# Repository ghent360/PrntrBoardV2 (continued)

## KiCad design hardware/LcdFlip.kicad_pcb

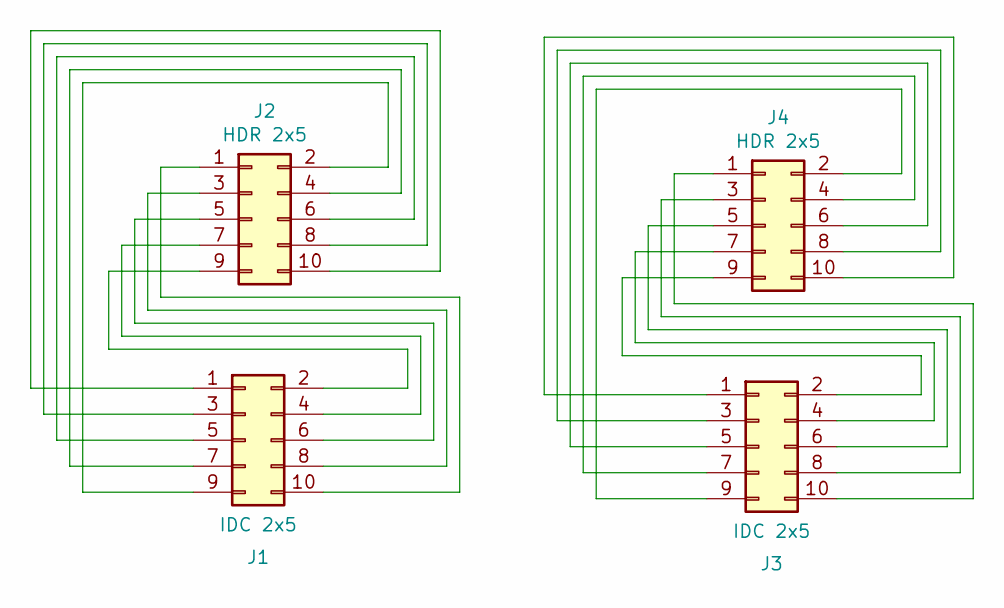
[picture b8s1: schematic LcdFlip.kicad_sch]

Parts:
J1, J3: IDC 2x5
J2, J4: HDR 2x5

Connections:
unnamed: J1.1, J2.10
unnamed: J1.2, J2.9
unnamed: J1.3, J2.8
unnamed: J1.4, J2.7
unnamed: J1.5, J2.6
unnamed: J1.6, J2.5
unnamed: J1.7, J2.4
unnamed: J1.8, J2.3
unnamed: J1.9, J2.2
unnamed: J1.10, J2.1
unnamed: J3.1, J4.10
unnamed: J3.2, J4.9
unnamed: J3.3, J4.8
unnamed: J3.4, J4.7
unnamed: J3.5, J4.6
unnamed: J3.6, J4.5
unnamed: J3.7, J4.4
unnamed: J3.8, J4.3
unnamed: J3.9, J4.2
unnamed: J3.10, J4.1

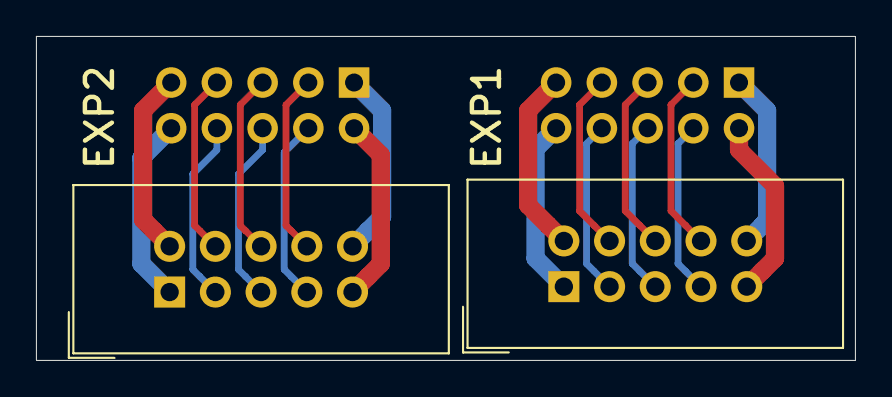
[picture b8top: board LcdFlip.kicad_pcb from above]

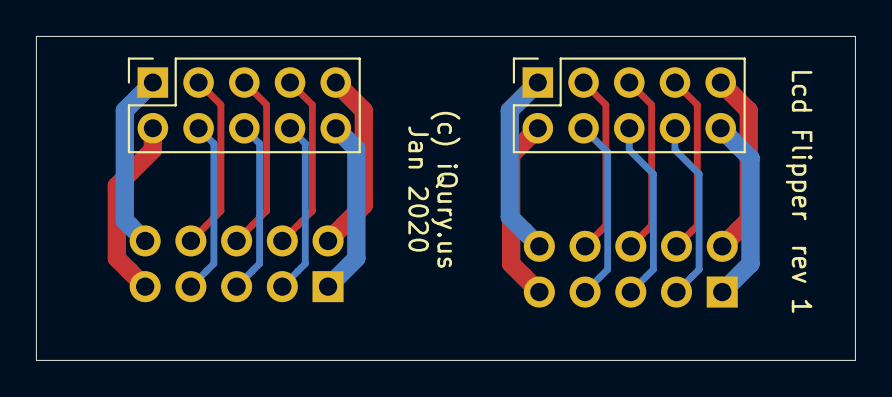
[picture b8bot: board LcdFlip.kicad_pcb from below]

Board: 2 copper layers, 45.5 x 18.0 mm, 4 parts (2 on the bottom side), 20 nets.

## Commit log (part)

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2019-09-30 Add CC BY-SA 3.0.
2019-09-30 Add common components shared with other boards.
2019-09-30 Move all hardware design files to the hardware folder.
2019-09-30 Aded basic 2660 schematics. Added library tables.
2019-09-30 Add PCM layout.
2019-10-02 Routed TMC2660 driver in the new pluggable form factor.
2019-10-03 Add mount holes on the bottom.
2019-10-06 Added TMC2209 driver.
2019-10-07 Add TMC2209 driver 2 layer rev1.
2019-10-12 Added open-drain buffer on the ALARM1 line.
2019-10-13 Add empty carrier board project.
2019-10-18 Added EEPROM.
2019-10-20 Re-organized schematics into hierarchical sheets. Added ADC inputs.
2019-10-20 Saved updates.
2019-10-20 Added endstops.
2019-10-20 Run annotation.
2019-10-20 Added servo connectors.
2019-10-20 Added stepper connectors.
2019-10-20 Run annotate.
2019-10-20 Fix annotations for U6 parts.
2019-10-20 Remove extra labels from the stepper driver wires.
2019-10-20 Assign footprints. All except the PCIe connectors.
2019-10-20 Assign all footprints.
2019-10-20 Fix foorprint library name.
2019-10-21 Update 3D models for components. Switch thermistors to JST connectors.
2019-10-21 Rename LCD connectors.
2019-10-21 Placed more RC components next to the respective connectors.
2019-10-21 Position more connectors.
2019-10-21 Getting closer to placing all components.
2019-10-21 Initial placement complete.
2019-10-21 Adde mounting holes to the PCIe connectors. Hide all references.
2019-10-22 Move driver holes a bit. Fix OSHW logo to appear.
2019-10-22 Update rev of drv2209
2019-10-25 Route some traces.
2019-10-25 Route more traces.
2019-10-26 115 unrouted traces left.
2019-10-26 100 unrouted traces left.
2019-10-26 89 unrouted traces left.
2019-10-26 65 tracks to go. Fixed DRC issues.
2019-10-26 50 unrouted traces to go.
2019-10-27 40 unrouted traces.
2019-10-27 15 unrouted traces.
2019-10-27 All routed!!!
2019-10-27 Verification rev 1.
2019-10-27 Start rev 2.
2019-10-27 What is more embarasin than a typo on the silk screen?
2019-10-27 Update the gerber files with the fixed typo.
2019-10-27 Fixed README.
2019-10-27 Added CPU to the features.
2019-10-27 Fix 5V fan location.
2019-10-27 Update silkscreen labels.
2019-10-27 Update 2660 fabrication files.
2019-10-29 Fix component values.
2019-10-29 Update PCB from schematics.
2019-10-29 Update CPU crystal to 5032 size.
2019-10-31 Added tracker to README.md.
2019-10-31 Fix layout of README.md.
2019-10-31 Added silk screen for Fuse values. Moved labels around.
2019-11-02 Make power lines thicker.
2019-11-03 Generate fabrication files.
2019-11-03 Update rev# and (c) date.
2019-11-04 Replace 74HCT02 with 74HCT04.
2019-11-06 Flip endstop signals to match RAMPS variants.
2019-11-06 Added 4 more permanent fan connectors.
2019-11-06 Update the current sense resistors on the 2660 driver to 2532 size.
2019-11-08 Add schematics PDB file.
2019-11-08 Remove extra library from the library table.
2019-11-08 Update schematics PDF.
2019-11-09 Update 3d model path and adjust offset to match the footprints.
2019-11-10 Fix more 3D foorprint paths.
2019-11-10 Update all 3d foorptints to point to the local project folder.
2019-11-10 Update EEPROM foorprint.
2019-11-11 Add I2C EEPROM to the 2209 driver board for identification.
2019-11-11 Update drv2209 to rev 5.
2019-11-12 Add some parts metadata.
2019-11-12 Added metadata for all Capacitors.
2019-11-12 Add metadata for resistors.
2019-11-12 Add metadata for the rest fo the components.
2019-11-12 Update control board gerber files.
2019-11-17 Remove some vias on the 2209 driver.
2019-11-17 Update 2209 rev to 6.
2019-11-17 Update QFN footprint to match the Trinamic spec.
2019-11-18 Update resistor values.
2019-11-22 Update TMC2209 DRC to 6mil spec.
2019-11-22 Add missing fab files.
2019-11-24 Update README.
2019-11-25 Swap EXP2 & EXP1 locations again.
2019-11-25 Mode 3d models to their own folder.
2019-11-25 Add power module based on XL1509.
2019-11-26 Added experimental power module based on MP1584.
2019-11-26 Update inductor for the MP1584 power supply.
2019-11-26 Update buck convertor footprint, so check if the new MP module would fit the board profile.
2019-11-26 Fix layer on solder pad oppenings.
2019-11-30 Update MP-Power design with a 3.2A inductor.
2019-11-30 Fix broken text labels.
2019-12-02 Add pulldown on ST_ENABLE signal.
2019-12-02 Change the ST_ENABLE to pull up as it is active low.
2019-12-02 Fix D21, it had incorrect foorprint.
2019-12-07 Re-route USB data lines, the diff pair was damaged after adding EXP4.
2019-12-08 Add schematics for the drivers in teh doc/ folder.
2019-12-08 Updated reverse voltage protection.
2019-12-08 Use the proper footpring for TO-252
2019-12-08 Add JLC tooling holes. Re-generate fabrication files.
2019-12-09 Added more dimensions.
2019-12-12 Route one missed trace.
2019-12-12 Copy the power converter.
2019-12-12 7 unrouted traces left.
2019-12-13 Add new diode package.
2019-12-13 Select better schottky diode.
2019-12-13 Generated gerber files.
2019-12-15 Generate production files.
2019-12-15 Update revision.
2019-12-19 Prepare the TMC2209 driver for production. Order 10 samples.
2019-12-19 Switch to the correct LCSC part for the gate.
2019-12-24 Update libraries to match the latest Windows release. Fix DRC issues.
2020-02-23 Update 2209 layout.
2020-02-23 Updated CPU.
2020-02-24 Separate VDDa from VDD. Update version labels.
2020-02-24 Update schematics to handle 8 stepper motors.
2020-02-24 Update VDDa connection. Update the revision and (c) date.
2020-02-25 Update board features.
2020-02-29 Updated VDDa power.
2020-03-01 Add electrolytic CAP on the drivers.
2020-03-01 Add thermal pad on the eeprom.
2020-03-01 Add electrolytic cap to the driver.
2020-03-01 Add TMC2130 driver (up to 42V).
2020-03-01 Route the 2130 driver board.
2020-03-02 Add mouning holes to the 2209 driver.
2020-03-02 Remove the mounting holes from the 2209 driver. SHould be used on a panel.
2020-03-02 Updated readme.
2020-03-10 Generate fabrication files for the 2130 driver. Set all JPCPCB properties.
2020-03-10 Fix DRC warnings. Update U3 metadata.
2020-03-10 U3->U2
2020-03-22 Update the TMC2660 driver with JLCPCB part numbers.
2020-04-09 Update TMC2660 pcb.
2020-04-14 Generate pos file in MM.
2020-04-14 Add IC pin mark. Generate pos file in MM.
2020-04-14 Re-generate TMC2209 gerbers. Have to update the JPC component info.
2020-05-02 Update the 24lc02 symbol. Add pad pin.
2020-05-03 Update TMC2130 layout add more power filter caps.
2020-05-03 Move one connector label for better readability.
2020-05-03 Move some NC designators on the schematics so they touch the pins.
2020-05-04 Added external clock source and routed it to the Stepper. Make the TMC2130 use the external clock.
2020-05-23 Updated driver PCBs.
2020-05-30 Only 130 DRC violations to clear...
2020-07-15 Removed some weird gnd vias.
2020-09-06 Minor layout updates.
2020-09-06 Rotate 3.3V regulator. Improve the 3.3V layout.
2020-10-08 Update to the latest daily Kicad. Fix board outline issue on PrntrBoardV2.
2020-11-01 Improve labels. Update to latest KiCAD format.
2020-11-01 Updated DRC rules. Fix labels.
2020-11-09 Enter schematics for T12 solder iron controller.
2020-11-14 Routhe the T12 Iron controller.
2020-11-14 Added LCSC Part #s Generated fab files.
2020-11-14 Fix edge file name.
2020-11-14 Revert the resistor networks back to 4x0402 footprint, not using JLC assembly svc for now.
2020-11-15 Update 2660 and 2130 driver fab files.
2020-11-19 Do length matching on the SD-card lines, to prevent issues with 4b SDIO mode.
2020-11-19 Revert "Do length matching on the SD-card lines, to prevent issues with 4b SDIO mode."
    This reverts commit da3406b2e34481ff4c80c4903b4a4e071462965b.
2020-12-02 Add more input protection. 480 ohm resistors on all direct IO pins. Clamping diodes on the endstops.
2020-12-02 Add new components to schematics.
2020-12-02 Revert "Add more input protection. 480 ohm resistors on all direct IO pins."
    This reverts commit 49fdbd5165b8c1709549cdf3235e4b40c9a44330.
2020-12-02 Update to latest kicad files.
2020-12-20 Update the 1N4148 diodes to B5819W. The 1N was too puny to serve as protection.
2021-01-01 Added jumper for the TMC2209 driver clock selection.
2021-01-01 Switch to TMC2209 rev9.
2021-01-15 5V terminal added
    - dedicated input of 5V to allow control of external 24V supply
    - minotr tracks adjustment / cleaning
2021-01-16 Added CAN
    - Added CAN interface (PD0-1) with RJ 6p6c terminal
    - SD card moved to back /left side and switched to SPI mode
    - removed EXP4 headrr
2021-01-16 Cleanup schematics.
2021-01-16 Fix DRC violation.
2021-01-16 Updated readme again.
2021-01-16 Fix typo.
2021-01-16 More typos.
2021-01-16 WiFI Addon
    Using ESP-12F module (supporting RRF DWC)
2021-01-16 Wifi adapter
2021-01-17 Correcting footprint, and adding manufacturing markers
    Gerber files & interactive BOM generated
2021-01-17 Correction of header placement
    Proper layer and spacing.
    Plus small jumper to select USB or VIN power for WIFi
2021-01-17 Add LCDFlip schematics.
2021-01-17 Add add-on board max dimensions and obstacles drawing.
2021-01-17 Added some more information to schema
    Added datasheet links to ESP-12F and ESP8266EX
    Some additional info on schematics and repositioning of resistors for better understed of their purpose.
2021-01-17 Initial commit for folder restructure #8
2021-01-17 DRV-Stepstick
    Simple driver to use spare StepSticks.
    Cheap in production,.
2021-01-18 Add manufactoring files for TMC2209 driver r8 (latest stable version).
2021-01-18 Add manufacturing files for TMC2660 r6.
2021-01-18 Add manufacturing files for TMC2130 r2.
2021-01-18 Add 3D printed driver mount feet. 2x per driver board.
2021-01-18 Add some pictures to document how to mount the driver boards.
2021-01-18 Routed the StepStick adapter board 2 layers.
2021-01-18 Small pcb corections
    - populated GND vias around the pcb
    - updated copyright info
2021-01-18 Update StepStick manufactirung files. Change copper zones with thermal relief. Added manufacturing scripts.
2021-01-18 Wire sd-card to SPI1, add sd_card_ss (~SD_CS) pin. Add EXP_CD pin for EXP2.4. Add dedicated EXP_SS pin for EXP2.7 - no longer has to share ~SD_DETECT. Added new pin ~EXP_CS2, replaced 3.3V supply on 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
    Removed 3.3V power supply from extension header. The 3.3V power supply is
    very limited (500mA) and we need it clean for the ADCs to work well.
2021-01-18 PCB Routing of changes in #10
2021-01-18 Make the CAN shielding ground components optional.
2021-01-18 Route the additional pull-up resistor.
2021-01-19 Move the configuration jumpers out of the way.
2021-01-19 Update interactive BOM.
2021-01-19 Update board.
2021-01-19 Add JST 4 pin right-angle motor connector model.
2021-01-19 Removal of leftovers
2021-01-19 Update of PCBs
    - added tooling holes
    - added order number location under components
    Updated projects:
    - DRV-Stepstick
    - TMC2209
    - TMC2130
2021-01-19 Update TMC2130_Driver.kicad_pcb
    missing pcb file
2021-01-25 Add proper CAN socket
    Push of Wurth 615006143421 socket corrected according to Wirth specification.
    No more optional parts, resistors & cap added to PCB.
    (some othe rminor file changes as I have opened the project in fresh Kicad 6 buid)
2021-02-02 Updated soldering iron board.
2021-02-02 Start Soldering Iron r3.
2021-02-02 Improve power supply filtering.
2021-02-02 Start soldering Iron rev 4.
2021-02-02 Added more ferrite beads to critical power lines.
2021-05-09 Toolboard initial version.
2021-05-09 Added endstops, adc, pwm, dirver and power.
2021-07-19 Update toolboard.
2021-07-19 Switch iron to 4 layer. Add dedicated GNDA signal.
2021-07-19 Update Iron gerbers, start new Iron revision.
2021-07-31 Add VSON footprint.
2021-08-17 Update Kicat project file to latest binary version.
2021-08-17 Update readme - add Klipper firmware support.
2021-08-26 Improve ADC ground: add separate GNDA bus; add ferrite bead to AVREF power.
2021-10-11 Generate fabrication files for Rev 5.
2021-10-11 Update Placement file.
2021-10-17 Update drivers to respect high motor coltage circuit.
